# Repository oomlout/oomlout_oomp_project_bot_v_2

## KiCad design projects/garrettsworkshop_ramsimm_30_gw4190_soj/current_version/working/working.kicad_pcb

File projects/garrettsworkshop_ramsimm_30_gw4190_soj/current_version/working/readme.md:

# ramsimm_30
 
## summary 
* id: garrettsworkshop_ramsimm_30_gw4190_soj
* user: garrettsworkshop
* name: ramsimm_30
* board: gw4190_soj
* repo: https://github.com/garrettsworkshop/RAMSIMM-30
* src_file_repo_kicad_pcb: GW4190-4MB-SOJ/GW4190-SOJ.kicad_pcb
* src_file_repo_kicad_pcb_link: https://github.com/garrettsworkshop/RAMSIMM-30/tree/release/GW4190-4MB-SOJ/GW4190-SOJ.kicad_pcb
* src_file_repo_kicad_sch: GW4190-4MB-SOJ/GW4190-SOJ.kicad_sch
* src_file_repo_kicad_sch_link: https://github.com/garrettsworkshop/RAMSIMM-30/tree/release/GW4190-4MB-SOJ/GW4190-SOJ.kicad_sch

* src_file_repo_sch: 
* src_file_repo_sch_link: https://github.com/garrettsworkshop/RAMSIMM-30/tree/release/
* full details link: https://github.com/oomlout/oomlout_oomp_project_bot_v_2/tree/main/projects/garrettsworkshop_ramsimm_30_gw4190_soj/current_version/working

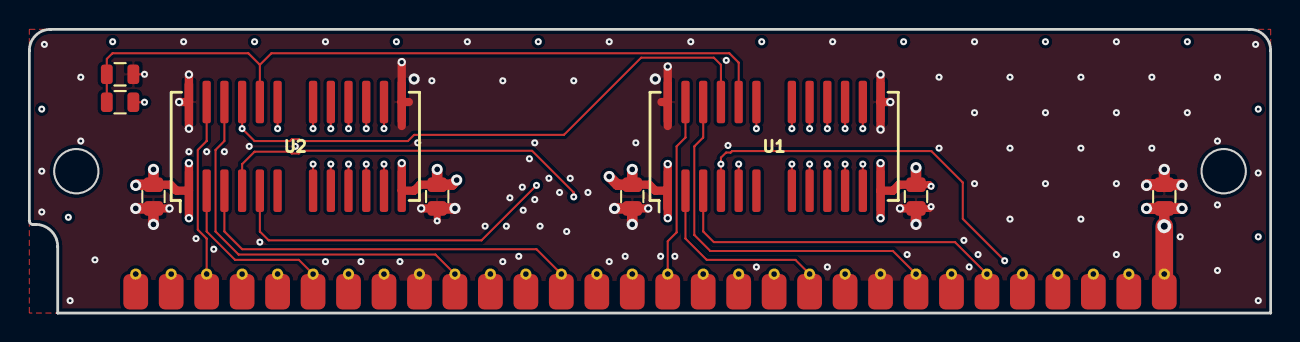
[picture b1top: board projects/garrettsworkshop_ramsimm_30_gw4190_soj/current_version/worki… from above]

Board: 4 copper layers, 88.9 x 20.3 mm, 10 parts (0 on the bottom side), 25 nets.

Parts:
C1, C2, C3, C4, C5: 2u2; C_0805
J1: DRAM-SIMM-30; SIMM-30_Edge
R1: EDO; R_0805
R2: FPM; R_0805
U1, U2: 4C4M4; SOJ-24-26_300mil

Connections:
+5V: C1.1, C2.1, C3.1, C4.1, C5.1, J1.1, J1.30, U1.1, U1.13, U2.1, U2.13
/1A0: J1.15, U1.9, U2.11
/1A1: J1.12, U1.10, U2.10
/1A2: J1.8, U1.11, U2.9
/1A3: J1.5, U1.12, U2.8
/1A4: J1.4, U1.15, U2.21
/1A5: J1.7, U1.16, U2.19
/1A6: J1.11, U1.17, U2.18
/1A7: J1.14, U1.18, U2.17
/1A8: J1.17, U1.19, U2.16
/1A9: J1.19, U1.21, U2.15
/1A10: J1.18, U1.8, U2.12
/D0: J1.3, U2.25
/D1: J1.6, U2.2
/D2: J1.10, U2.24
/D3: J1.13, U2.3
/D4: J1.16, U1.25
/D5: J1.20, U1.2
/D6: J1.23, U1.24
/D7: J1.25, U1.3
/~CAS: J1.2, R1.1, U1.23, U2.23
/~OE: R1.2, R2.1, U1.22, U2.22
/~RAS: J1.27, U1.5, U2.5
/~WE: J1.21, U1.4, U2.4
GND: C1.2, C2.2, C3.2, C4.2, C5.2, J1.9, J1.22, R2.2, U1.14, U1.26, U2.14, U2.26

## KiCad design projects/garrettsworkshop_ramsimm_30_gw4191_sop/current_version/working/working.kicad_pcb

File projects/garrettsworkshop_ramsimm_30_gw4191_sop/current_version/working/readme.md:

# ramsimm_30
 
## summary 
* id: garrettsworkshop_ramsimm_30_gw4191_sop
* user: garrettsworkshop
* name: ramsimm_30
* board: gw4191_sop
* repo: https://github.com/garrettsworkshop/RAMSIMM-30
* src_file_repo_kicad_pcb: GW4191-4MB-parity-SOP/GW4191-SOP.kicad_pcb
* src_file_repo_kicad_pcb_link: https://github.com/garrettsworkshop/RAMSIMM-30/tree/release/GW4191-4MB-parity-SOP/GW4191-SOP.kicad_pcb
* src_file_repo_kicad_sch: GW4191-4MB-parity-SOP/GW4191-SOP.kicad_sch
* src_file_repo_kicad_sch_link: https://github.com/garrettsworkshop/RAMSIMM-30/tree/release/GW4191-4MB-parity-SOP/GW4191-SOP.kicad_sch

* src_file_repo_sch: 
* src_file_repo_sch_link: https://github.com/garrettsworkshop/RAMSIMM-30/tree/release/
* full details link: https://github.com/oomlout/oomlout_oomp_project_bot_v_2/tree/main/projects/garrettsworkshop_ramsimm_30_gw4191_sop/current_version/working

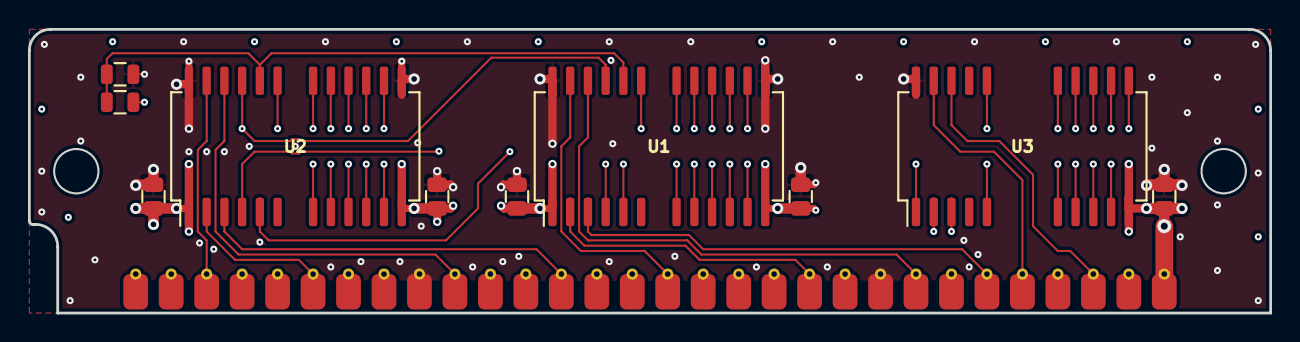
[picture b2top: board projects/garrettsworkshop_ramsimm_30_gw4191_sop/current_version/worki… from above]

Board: 4 copper layers, 88.9 x 20.3 mm, 11 parts (0 on the bottom side), 28 nets.

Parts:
C1, C2, C3, C4, C5: 2u2; C_0805
J1: DRAM-SIMM-30; SIMM-30_Edge
R1: EDO; R_0805
R2: FPM; R_0805
U1, U2: 4C4M4; SOP-24-26_300mil
U3: 4C4M1; SOP-20-26_300mil

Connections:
+5V: C1.1, C2.1, C3.1, C4.1, C5.1, J1.1, J1.30, U1.1, U1.13, U2.1, U2.13, U3.13
/1A0: J1.15, U1.9, U2.11, U3.9
/1A1: J1.12, U1.10, U2.10, U3.10
/1A2: J1.8, U1.11, U2.9, U3.11
/1A3: J1.5, U1.12, U2.8, U3.12
/1A4: J1.4, U1.15, U2.21, U3.14
/1A5: J1.7, U1.16, U2.19, U3.15
/1A6: J1.11, U1.17, U2.18, U3.16
/1A7: J1.14, U1.18, U2.17, U3.17
/1A8: J1.17, U1.19, U2.16, U3.18
/1A9: J1.19, U1.21, U2.15, U3.5
/1A10: J1.18, U1.8, U2.12, U3.22
/D0: J1.3, U2.25
/D1: J1.6, U2.2
/D2: J1.10, U2.24
/D3: J1.13, U2.3
/D4: J1.16, U1.25
/D5: J1.20, U1.2
/D6: J1.23, U1.24
/D7: J1.25, U1.3
/DP: J1.29, U3.1
/QP: J1.26, U3.25
/~CASP: J1.28, U3.24
/~CAS: J1.2, R1.1, U1.23, U2.23
/~OE: R1.2, R2.1, U1.22, U2.22
/~RAS: J1.27, U1.5, U2.5, U3.3
/~WE: J1.21, U1.4, U2.4, U3.2
GND: C1.2, C2.2, C3.2, C4.2, C5.2, J1.9, J1.22, R2.2, U1.14, U1.26, U2.14, U2.26, U3.26

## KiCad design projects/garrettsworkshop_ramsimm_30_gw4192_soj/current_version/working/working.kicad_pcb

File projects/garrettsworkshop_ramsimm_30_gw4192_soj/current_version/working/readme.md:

# ramsimm_30
 
## summary 
* id: garrettsworkshop_ramsimm_30_gw4192_soj
* user: garrettsworkshop
* name: ramsimm_30
* board: gw4192_soj
* repo: https://github.com/garrettsworkshop/RAMSIMM-30
* src_file_repo_kicad_pcb: GW4192-16MB-SOJ/GW4192-SOJ.kicad_pcb
* src_file_repo_kicad_pcb_link: https://github.com/garrettsworkshop/RAMSIMM-30/tree/release/GW4192-16MB-SOJ/GW4192-SOJ.kicad_pcb
* src_file_repo_kicad_sch: GW4192-16MB-SOJ/GW4192-SOJ.kicad_sch
* src_file_repo_kicad_sch_link: https://github.com/garrettsworkshop/RAMSIMM-30/tree/release/GW4192-16MB-SOJ/GW4192-SOJ.kicad_sch

* src_file_repo_sch: 
* src_file_repo_sch_link: https://github.com/garrettsworkshop/RAMSIMM-30/tree/release/
* full details link: https://github.com/oomlout/oomlout_oomp_project_bot_v_2/tree/main/projects/garrettsworkshop_ramsimm_30_gw4192_soj/current_version/working

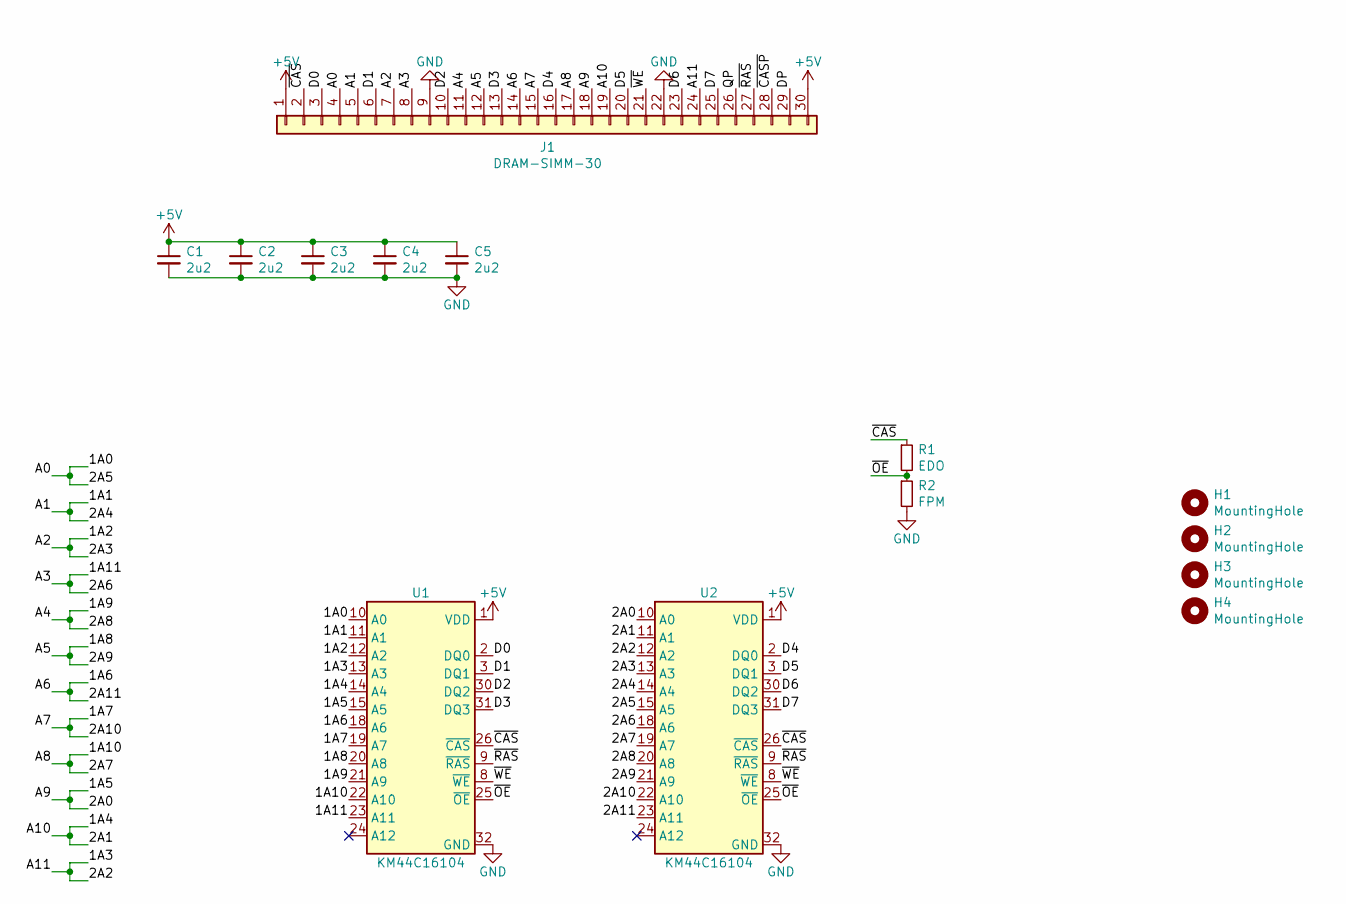
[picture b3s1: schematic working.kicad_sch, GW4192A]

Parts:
C1, C2, C3, C4, C5: 2u2; C_0805
H1, H2, H3, H4: MountingHole; PasteHole_1.152mm_NPTH
J1: DRAM-SIMM-30; SIMM-30_Edge
R1: EDO; R_0805
R2: FPM; R_0805
U1, U2: KM44C16104; SOJ-32_400mil

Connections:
+5V: C1.1, C2.1, C3.1, C4.1, C5.1, J1.1, J1.30, U1.1 (VDD), U1.16 (VDD), U2.1 (VDD), U2.16 (VDD)
/1A0: J1.4, U1.10 (A0), U2.15 (A5)
/1A1: J1.5, U1.11 (A1), U2.14 (A4)
/1A2: J1.7, U1.12 (A2), U2.13 (A3)
/1A3: J1.24, U1.13 (A3), U2.12 (A2)
/1A4: J1.19, U1.14 (A4), U2.11 (A1)
/1A5: J1.18, U1.15 (A5), U2.10 (A0)
/1A6: J1.14, U1.18 (A6), U2.23 (A11)
/1A7: J1.15, U1.19 (A7), U2.22 (A10)
/1A8: J1.12, U1.20 (A8), U2.21 (A9)
/1A9: J1.11, U1.21 (A9), U2.20 (A8)
/1A10: J1.17, U1.22 (A10), U2.19 (A7)
/1A11: J1.8, U1.23 (A11), U2.18 (A6)
/D0: J1.3, U1.2 (DQ0)
/D1: J1.6, U1.3 (DQ1)
/D2: J1.10, U1.30 (DQ2)
/D3: J1.13, U1.31 (DQ3)
/D4: J1.16, U2.2 (DQ0)
/D5: J1.20, U2.3 (DQ1)
/D6: J1.23, U2.30 (DQ2)
/D7: J1.25, U2.31 (DQ3)
/DP: J1.29
/QP: J1.26
/~CASP: J1.28
/~CAS: J1.2, R1.1, U1.26 (~CAS), U2.26 (~CAS)
/~OE: R1.2, R2.1, U1.25 (~OE), U2.25 (~OE)
/~RAS: J1.27, U1.9 (~RAS), U2.9 (~RAS)
/~WE: J1.21, U1.8 (~WE), U2.8 (~WE)
GND: C1.2, C2.2, C3.2, C4.2, C5.2, J1.9, J1.22, R2.2, U1.17 (GND), U1.32 (GND), U2.17 (GND), U2.32 (GND)

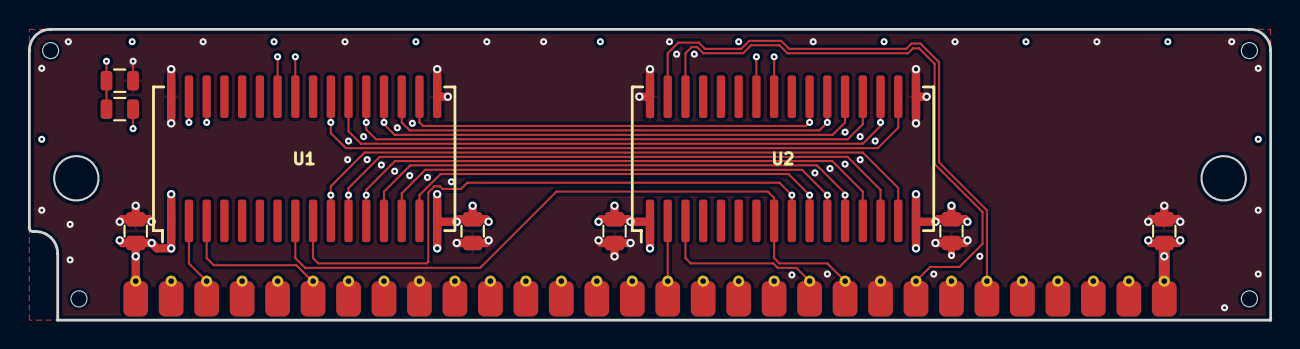
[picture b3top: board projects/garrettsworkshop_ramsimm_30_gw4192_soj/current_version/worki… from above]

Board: 4 copper layers, 88.9 x 20.8 mm, 14 parts (0 on the bottom side), 26 nets.
